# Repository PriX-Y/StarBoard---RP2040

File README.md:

# StarBoard---RP2040

its my own Open source **rp2040** devboard made with hackclub. its my first devboard project what i finnaly end

# Program what i use:

- Kicad -

# Datasheet what i use:

https://www.nextpcb.com/blog/compare-rp2040-rp2350

and little from tutorial:

https://stasis.hackclub.com/starter-projects/devboard
# suggestion 

if you wanna buy this you need use my cpl and bom version not becuse you need it but becuse i spend like 1 hours to seearch for the part id on jscs to get it on jlpcb so i to suggest use jlpcb

# cost

becuse i made in 2 layer is maybe cheap. but let know if you go only pcb  and self soldring this can be +- 40$ with parts i didt have hot air and hot plate so i go pcba way

there is full cost for me with delivery cost and duty for me to poland

there is cart

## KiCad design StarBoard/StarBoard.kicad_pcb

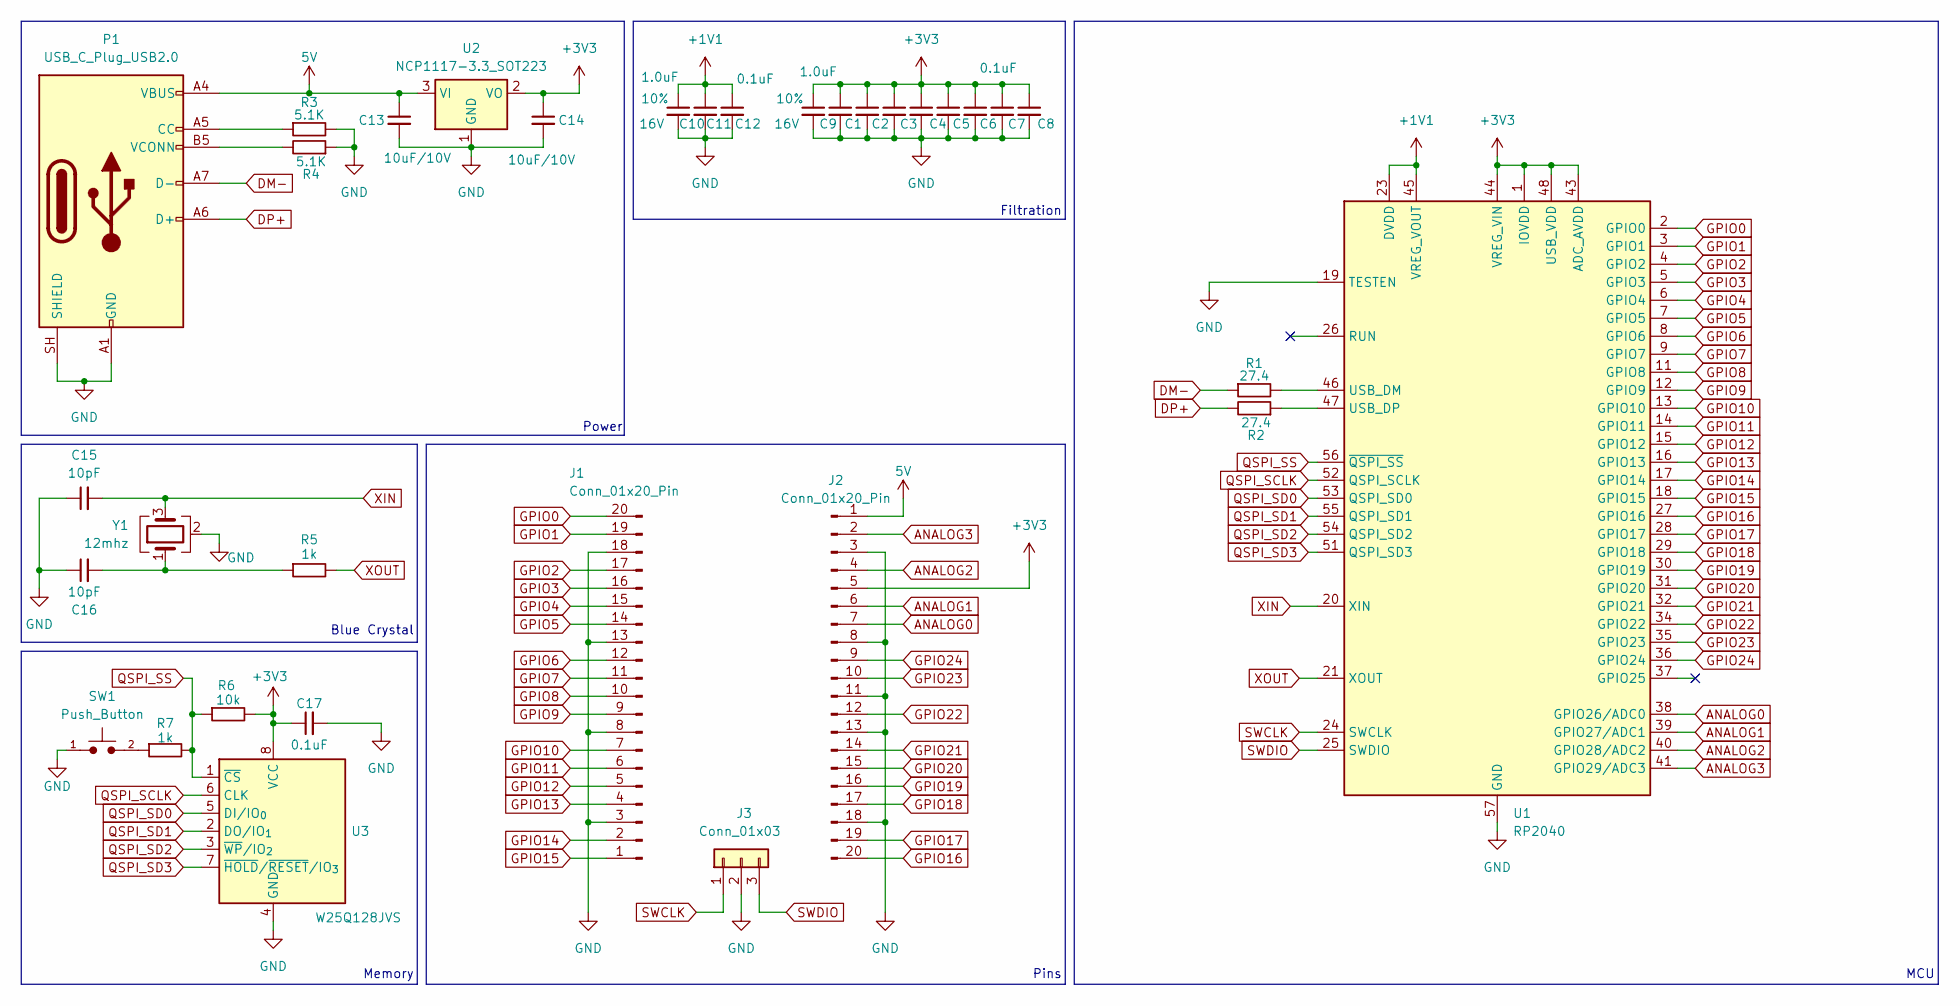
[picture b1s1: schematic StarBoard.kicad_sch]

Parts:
C1, C2, C3, C4, C5, C6, C7, C8, C11, C12: 0.1uF; C_0402_1005Metric; Voltage 16V; Tolerance 10%
C9, C10: 1.0uF; C_0402_1005Metric; Voltage 16V; Tolerance 10%
C13, C14: 10uF_0603_10V; C_0402_1005Metric; Part Number GRM188R61A106KE69D; JLCPCB ID C19702
C15, C16: 10pF; C_0603_1608Metric; Voltage 50V; Tolerance 5%
C17: 100nF_0603_16V; C_0402_1005Metric; Part Number 0603YC104KAT2A; JLCPCB ID C14663
J1, J2: Conn_01x20_Pin; PinHeader_1x20_P2.54mm_Vertical
J3: Conn_01x03; PinHeader_1x03_P2.54mm_Vertical; Part Number 1-0301FBV0T
P1: USB_C_Plug_USB2.0; USB_C_Receptacle_HRO_TYPE-C-31-M-12
R1, R2: 27.4; R_0402_1005Metric
R3, R4: 5.1K; R_0402_1005Metric
R5, R7: 1k; R_0402_1005Metric
R6: 10k; R_0402_1005Metric
SW1: Push_Button; SW_PUSH_6mm
U1: RP2040; QFN-56-1EP_7x7mm_P0.4mm_EP3.2x3.2mm
U2: NCP1117-3.3_SOT223; SOT-223-3_TabPin2
U3: W25Q128JVS; SOIC-8_5.3x5.3mm_P1.27mm
Y1: 12mhz; Crystal_SMD_3225-4Pin_3.2x2.5mm

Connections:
5V: C13.1, J2.1, P1.A4 (VBUS), P1.A9 (VBUS), P1.B4 (VBUS), P1.B9 (VBUS), U2.3 (VI)
+1V1: C10.1, C11.1, C12.1, U1.23 (DVDD), U1.45 (VREG_VOUT), U1.50 (DVDD)
ANALOG0: J2.7, U1.38 (GPIO26/ADC0)
ANALOG1: J2.6, U1.39 (GPIO27/ADC1)
ANALOG2: J2.4, U1.40 (GPIO28/ADC2)
ANALOG3: J2.2, U1.41 (GPIO29/ADC3)
DM-: P1.A7 (D-), R1.1
DP+: P1.A6 (D+), R2.2
GND: C1.2, C2.2, C3.2, C4.2, C5.2, C6.2, C7.2, C8.2, C9.2, C10.2, C11.2, C12.2, C13.2, C14.2, C15.1, C16.1, C17.2, J1.3, J1.8, J1.13, J1.18, J2.3, J2.8, J2.11, J2.13, J2.18, J3.2, P1.A1 (GND), P1.A12 (GND), P1.B1 (GND), P1.B12 (GND), P1.SH (SHIELD), R3.2, R4.1, SW1.1, U1.19 (TESTEN), U1.57 (GND), U2.1 (GND), U3.4 (GND), Y1.2 (G), Y1.4 (G)
GPIO0: J1.20, U1.2 (GPIO0)
GPIO1: J1.19, U1.3 (GPIO1)
GPIO2: J1.17, U1.4 (GPIO2)
GPIO3: J1.16, U1.5 (GPIO3)
GPIO4: J1.15, U1.6 (GPIO4)
GPIO5: J1.14, U1.7 (GPIO5)
GPIO6: J1.12, U1.8 (GPIO6)
GPIO7: J1.11, U1.9 (GPIO7)
GPIO8: J1.10, U1.11 (GPIO8)
GPIO9: J1.9, U1.12 (GPIO9)
GPIO10: J1.7, U1.13 (GPIO10)
GPIO11: J1.6, U1.14 (GPIO11)
GPIO12: J1.5, U1.15 (GPIO12)
GPIO13: J1.4, U1.16 (GPIO13)
GPIO14: J1.2, U1.17 (GPIO14)
GPIO15: J1.1, U1.18 (GPIO15)
GPIO16: J2.20, U1.27 (GPIO16)
GPIO17: J2.19, U1.28 (GPIO17)
GPIO18: J2.17, U1.29 (GPIO18)
GPIO19: J2.16, U1.30 (GPIO19)
GPIO20: J2.15, U1.31 (GPIO20)
GPIO21: J2.14, U1.32 (GPIO21)
GPIO22: J2.12, U1.34 (GPIO22)
GPIO23: J2.10, U1.35 (GPIO23)
GPIO24: J2.9, U1.36 (GPIO24)
unnamed: C16.2, R5.1, Y1.1
unnamed: P1.A5 (CC), R3.1
unnamed: P1.B5 (VCONN), R4.2
unnamed: R7.1, SW1.2
unnamed: R1.2, U1.46 (USB_DM)
unnamed: R2.1, U1.47 (USB_DP)
QSPI_SCLK: U1.52 (QSPI_SCLK), U3.6 (CLK)
QSPI_SD0: U1.53 (QSPI_SD0), U3.5 (DI/IO_{0})
QSPI_SD1: U1.55 (QSPI_SD1), U3.2 (DO/IO_{1})
QSPI_SD2: U1.54 (QSPI_SD2), U3.3 (~WP/IO_{2})
QSPI_SD3: U1.51 (QSPI_SD3), U3.7 (~HOLD/~RESET/IO_{3})
QSPI_SS: R6.1, R7.2, U1.56 (~QSPI_SS), U3.1 (~CS)
SWCLK: J3.1, U1.24 (SWCLK)
SWDIO: J3.3, U1.25 (SWDIO)
XIN: C15.2, U1.20 (XIN), Y1.3
XOUT: R5.2, U1.21 (XOUT)

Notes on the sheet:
MCU
Blue Crystal
Memory
Filtration
Power
Pins

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
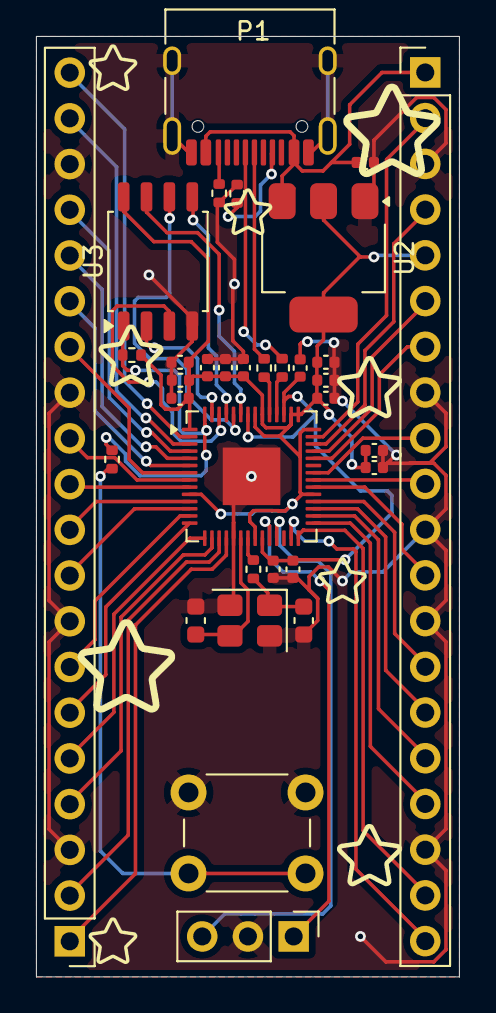
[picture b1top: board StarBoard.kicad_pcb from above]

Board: 2 copper layers, 23.5 x 52.2 mm, 33 parts (0 on the bottom side), 51 nets.
